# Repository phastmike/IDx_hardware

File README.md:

# YAESU DR-1X/DR-2X VOICE ID 

This project is a design of a Voice ID board for the YAESU DR-1X and 
DR-2X repeater models.

These repeaters do have a morse id feature and by using the FVS-2 voice module
they can do a very limited voice identification function which will synthetize
the repeater callsign and nothing else.

These repeaters provide a CONTROL I/O port with 15 pins and a ACC port with 10 
pins.

Both can be used but there is no documentation regarding the ACC serial data protocol.

The firmware is available in [this repository](https://github.com/phastmike/IDx)

## Hardware

This project is based around the Raspberry Pi Pico (RP2040). It uses some digital
GPIOs to control the repeater for voice identification purposes. The advantage of using the Pico and specially the Python SDK is that the filesystem is already there amongst others.

Via the Control IO port we can get many control signals from the repeater and the
logic interface is direct with not so many discrete components.

The circuit can be powered from usb and from the radio, simultaneaously if needed.

The circuit is simple. A regulator for voltage control, leds and the resistor divider
for volume control with a simple 1st order RC filter.

### Pictures

- Inside the box

- A more detailed look at the PCB

### Schematic

The schematic is adapted to the real implementation in real life, that's why,
eg, the volume potentiometer appears as a JST/KK/Molex 3 pin conector.

**Check the PDFs for the schematic.**

#### Led connections

### Yaesu DR1-X

The Yaesu DR1X has some design flaws in the controller board.

From the technical manual we can see that some transistor were not fitted and
some resistor values were incorrect, eg, the 0 ohm resitor in the CTCSS zener protector.

#### Control IO Pinout

|Pin No|Pin Name|I/O Descriptions|
|------|--------|----------------|
|1|EXT I/O|Input [L] GND: Remote mode   [H] OPEN: Repeater mode|
|2|PTT|Input [L] GND: EXT PTT ON   [H] OPEN: EXT PTT OFF When this pin is pulled low by an external device, it keys the repeater transmitter. |
|3|CTCSS/DCS (PKSQL)|Output [L] GND: Decoded   [H] OPEN: Un-decoded / Signaling settings in the repeater setup menu will be applied.|
|4|SQL DET (Noise SQL)|Output [L] GND: SQL open   [H] OPEN: SQL close / This is an open-collector, active-low output capable of sinking about 10 mA. It indicates that the receiver squelch is open. If the squelch control is properly set, this indicates a carrier on the receiver channel.|
|5|GND|GND Chassis ground for all logic levels and power supply return |
|6|TONE IN|Input CTCSS/DCS EXT input / 600 ohm, 500 mV peak to peak, Valid during external PTT control. This pin is sub-audible tone input, and has a flat response characteristic (repeater deviation is constant for a given signal level over the frequency range of 5 ~ 250 Hz). Injecting a too high signal level here causes over-deviation of CTCSS or DCS, degrading performance. Use shielded cable to connect to this pin, connecting the shield to GND.
|7|AF IN|Input EXT Modulation input / 600 ohm, 1.5 V peak to peak / Valid during external PTT control / This pin is audio input (300 ~ 3,000 Hz). This audio is injected before the splatter filter stage, so excess signal input levels are clipped. It is impossible to input analog modulation signals and convert them to digital signals on DR-1X/DR-1XE. Use shielded cable to connect to this pin, and connect the shield to GND.
|8|DISC OUT|Output Up-link RX DISC output (w/o de-emphasis), 500 mV peak to peak / Discriminator output during up-link reception. Does not affect the operation mode of the repeater. The signal is extracted before the de-emphasis and squelch circuitry. **Use shielded cable to connect to this pin, and connect the shield to GND.**|
|9|AF OUT|Output Up-link RX AF output (w/ de-emphasis), 300 mV peak to peak Analog audio output during up-link reception. Does not affect the operation mode of the repeater. This pin is an output for AF signal (300 mVp-p), being extracted after the de-emphasis. Demodulated digital signals can be output as well.
|10|GND|GND Chassis ground for all logic levels and power supply return|
|11|EXT1 *|Input. In Remote mode, the logic combination of Ports EXT1 and EXT2 determines the transmit and receive modes|
|12|EXT2 *|Input. **Check table below**|
|13|EXT3 *|Input [L] GND: RX Tone OFF   [H] OPEN: Setup mode. Input a low level signal to indicate that the receiving tone is invalid.|
|14|EXT4 *|Input [L] GND: TX Tone OFF   [H] OPEN: Setup mode. Input a low level signal to indicate that the transmitting tone is invalid.|
|15|VCC|VCC Power supply. This pin provides 13.8 V, 2.0 A, DC from the repeater supply. There is an internal 3 A fuse to prevent damage to the repeater.|

\*) *These functions may only be activated while the repeater is in Remote mode.*

|Port 2|Port 1|RX|TX|
|------|------|---|---|
|H|H|Auto (AMS)|FM|
|H|L|FM|FM|
|L|H|Digital|Digital|
|L|L|Auto (AMS)|Auto (AMS|

## Links

- https://ww8tf.club/yaesu-dr-1x-repeater-modification-common-concerns/
- http://c4fm.xyz/c4fm-radios/yaesu-dr-1-c4fm.php
- https://www.vk6uu.id.au/fusion-front.html
- https://www.arcomcontrollers.com/index.php/rc210/rc210-board
- http://www.repeater-builder.com/yvs/vxr-1000-to-dr-1x.html
- http://hamlabs.no/2015/05/28/interfacing-the-dr-1x-repeater/
- https://openrepeater.com/
- https://ics-ctrl.com/
- http://www.kk4ice.com/?page_id=621
- https://www.masterscommunications.com/products/radio-adapter/radr1x.html

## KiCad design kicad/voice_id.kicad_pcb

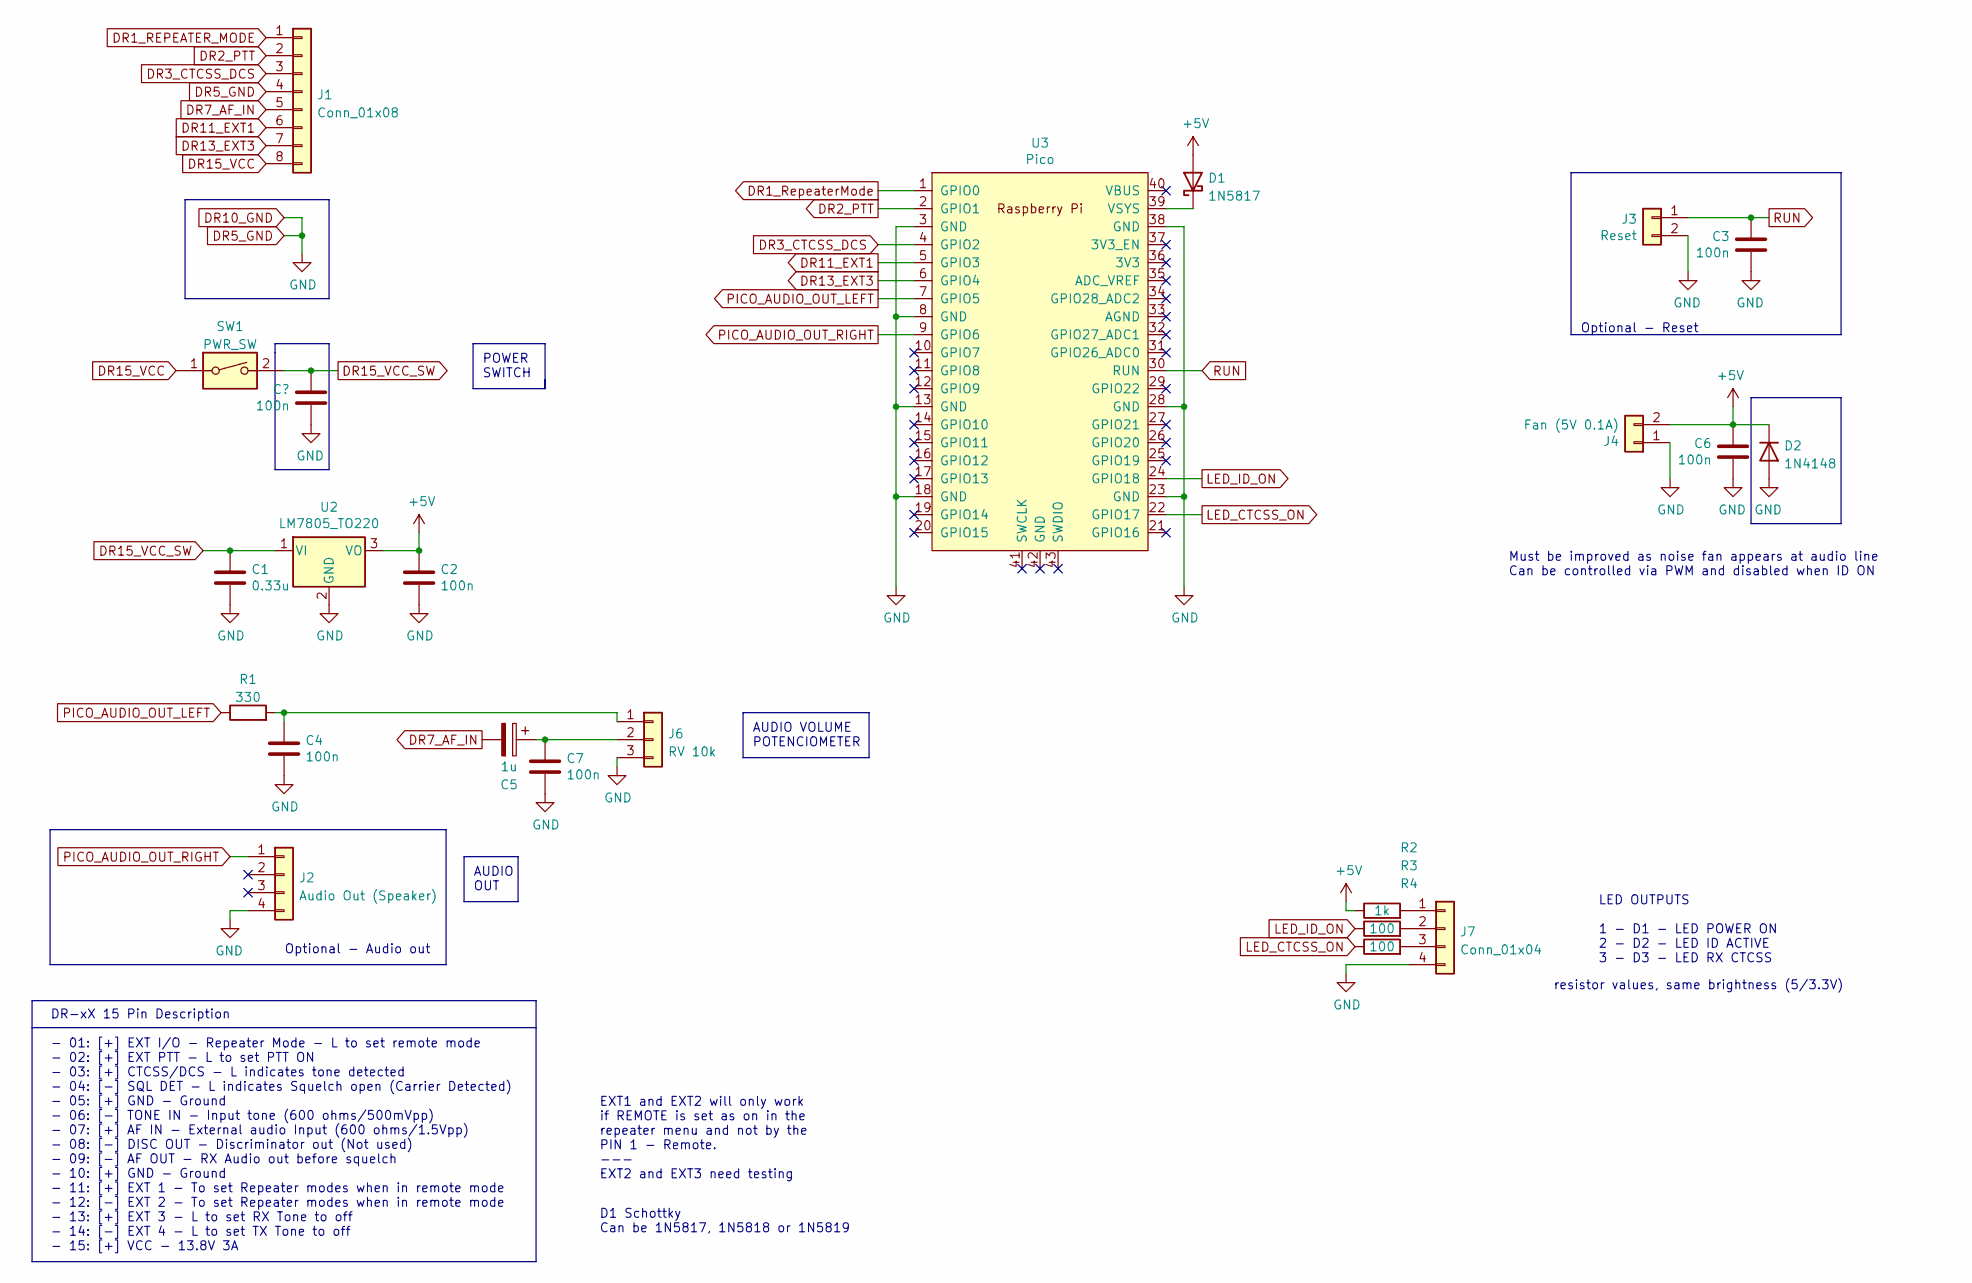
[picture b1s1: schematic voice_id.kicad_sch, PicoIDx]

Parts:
C1: 0.33u; CP_Radial_D5.0mm_P2.50mm
C2, C3, C4, C6, C7: 100n; C_Disc_D5.0mm_W2.5mm_P5.00mm
C5: 1u; C_Disc_D5.0mm_W2.5mm_P5.00mm
D1: 1N5817; D_DO-41_SOD81_P10.16mm_Horizontal
D2: 1N4148; D_DO-35_SOD27_P7.62mm_Horizontal
J1: Conn_01x08; Molex_KK-254_AE-6410-08A_1x08_P2.54mm_Vertical
J2: Audio Out (Speaker); PinHeader_1x04_P2.54mm_Vertical
J3: Reset; Molex_KK-254_AE-6410-02A_1x02_P2.54mm_Vertical
J4: Fan (5V 0.1A); Molex_KK-254_AE-6410-02A_1x02_P2.54mm_Vertical
J6: RV 10k; Molex_KK-254_AE-6410-03A_1x03_P2.54mm_Vertical
J7: Conn_01x04; Molex_KK-254_AE-6410-04A_1x04_P2.54mm_Vertical
R1: 330; R_Axial_DIN0207_L6.3mm_D2.5mm_P10.16mm_Horizontal
R2: 1k; R_Axial_DIN0207_L6.3mm_D2.5mm_P10.16mm_Horizontal
R3, R4: 100; R_Axial_DIN0207_L6.3mm_D2.5mm_P10.16mm_Horizontal
SW1: PWR_SW; Molex_KK-254_AE-6410-02A_1x02_P2.54mm_Vertical
U2: LM7805_TO220; TO-220-3_Vertical
U3: Pico; RPi_Pico_SMD_TH

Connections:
+5V: C2.1, C6.1, D1.2 (A), D2.1 (K), J4.2, R2.1, U2.3 (VO)
DR1_REPEATER_MODE: J1.1
DR1_RepeaterMode: U3.1 (GPIO0)
DR2_PTT: J1.2, U3.2 (GPIO1)
DR3_CTCSS_DCS: J1.3, U3.4 (GPIO2)
DR7_AF_IN: C5.2, J1.5
DR10_GND: C1.2, C2.2, C3.2, C4.2, C6.2, C7.2, D2.2 (A), J1.4, J2.4, J3.2, J4.1, J6.3, J7.4, U2.2 (GND), U3.3 (GND), U3.8 (GND), U3.13 (GND), U3.18 (GND), U3.23 (GND), U3.28 (GND), U3.38 (GND)
DR11_EXT1: J1.6, U3.5 (GPIO3)
DR13_EXT3: J1.7, U3.6 (GPIO4)
DR15_VCC: J1.8, SW1.1
DR15_VCC_SW: C1.1, SW1.2, U2.1 (VI)
LED_CTCSS_ON: R4.1, U3.22 (GPIO17)
LED_ID_ON: R3.1, U3.24 (GPIO18)
unnamed: C4.1, J6.1, R1.2
unnamed: C5.1, C7.1, J6.2
unnamed: D1.1 (K), U3.39 (VSYS)
unnamed: J7.1, R2.2
unnamed: J7.2, R3.2
unnamed: J7.3, R4.2
PICO_AUDIO_OUT_LEFT: R1.1, U3.7 (GPIO5)
PICO_AUDIO_OUT_RIGHT: J2.1, U3.9 (GPIO6)
RUN: C3.1, J3.1, U3.30 (RUN)

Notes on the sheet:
resistor values, same brightness (5/3.3V)
D1 Schottky Can be 1N5817, 1N5818 or 1N5819
EXT1 and EXT2 will only work if REMOTE is set as on in the repeater menu and not by the PIN 1 - Remote. --- EXT2 and EXT3 need testing
AUDIO OUT
Optional - Reset
LED OUTPUTS 1 - D1 - LED POWER ON 2 - D2 - LED ID ACTIVE 3 - D3 - LED RX CTCSS
Must be improved as noise fan appears at audio line Can be controlled via PWM and disabled when ID ON
AUDIO VOLUME POTENCIOMETER
Optional - Audio out
POWER SWITCH
DR-xX 15 Pin Description - 01: [+] EXT I/O - Repeater Mode - L to set remote mode - 02: [+] EXT PTT - L to set PTT ON - 03: [+] CTCSS/DCS - L indicates tone detected - 04: [-] SQL DET - L indicates Squelch open (Carrier Detected) - 05: [+] GND - Ground - 06: [-] TONE IN - Input tone (600 ohms/500mV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

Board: 2 copper layers, 22 parts (0 on the bottom side), 20 nets, no tracks yet.

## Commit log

2022-09-21 Added 100n capacitor to ctcss pin (c9)
2022-09-21 Added exported schematics, 1.1
2023-02-19 Added some images
2023-02-19 retuned img items
2023-08-16 Added info on led connections from our prototype
2024-03-02 added link to fw repo
